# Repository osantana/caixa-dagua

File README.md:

# Caixa d'Água

Automação para controle de poço e caixa d'água da chácara

## Módulo central

* ESP32-WROOM rodando MicroPython
* Display TFT 2.4" 320x240 com Touch (ILI9341 + XPT2046)
* Módulo de Rádio HC-12
* RTC DS1307

### Instalação hidráulica

* Bóia automática na caixa d'água

## Módulo de controle

* Arduino Nano
* Módulo de Rádio HC-12
* Módulo de Relés 4 canais

### Instalação hidráulica

* Válvula eletrica 3 vias 220V
* Bomba hidráulica 220V

# Protocolo de comunicação

* SOURCE_ID: byte (0x00 = central)
* TARGET_ID: byte (0x00 = central)
* CHAIN_SIZE: byte
* CHAIN: list[byte] (devices que repassaram o pacote)
* COMMAND:
  * 0x00: RESET (reseta target)
  * 0x01: SET (seta parâmetro)
    * KEY: pascal-str
    * VALUE: pascal-str
  * 0x02: GET (recupera parâmetro)
    * KEY: pascal-str
    * VALUE: pascal-str
  * 0x03: RESPONSE (parâmetro recuperado)
    * KEY: pascal-str
    * VALUE: pascal-str
  * 0x04: NOTIFY (notificação)
    * PRIORITY: byte
    * NOTIFICATION: pascal-str

  * 0x11: READ
    * SENSOR_ID: byte (número do sensor para ler)
  * 0x12: INFO
    * SENSOR_ID: byte (número do sensor lido)
    * DATA: pascal-str

  * 0x20: START:
    * CHANNEL: byte (número do canal a ser parado)
    * TIMEOUT: uint (número de segundos de funcionamento deve ser diferente de 0)
  * 0x21: STOP (parada forçada. só deve ser usado em emergência)
    * CHANNEL: byte (número do canal a ser parado. 0xFF = todos)

* PARAMETERS: (dependente do comando)
* CHECKSUM: (a definir)

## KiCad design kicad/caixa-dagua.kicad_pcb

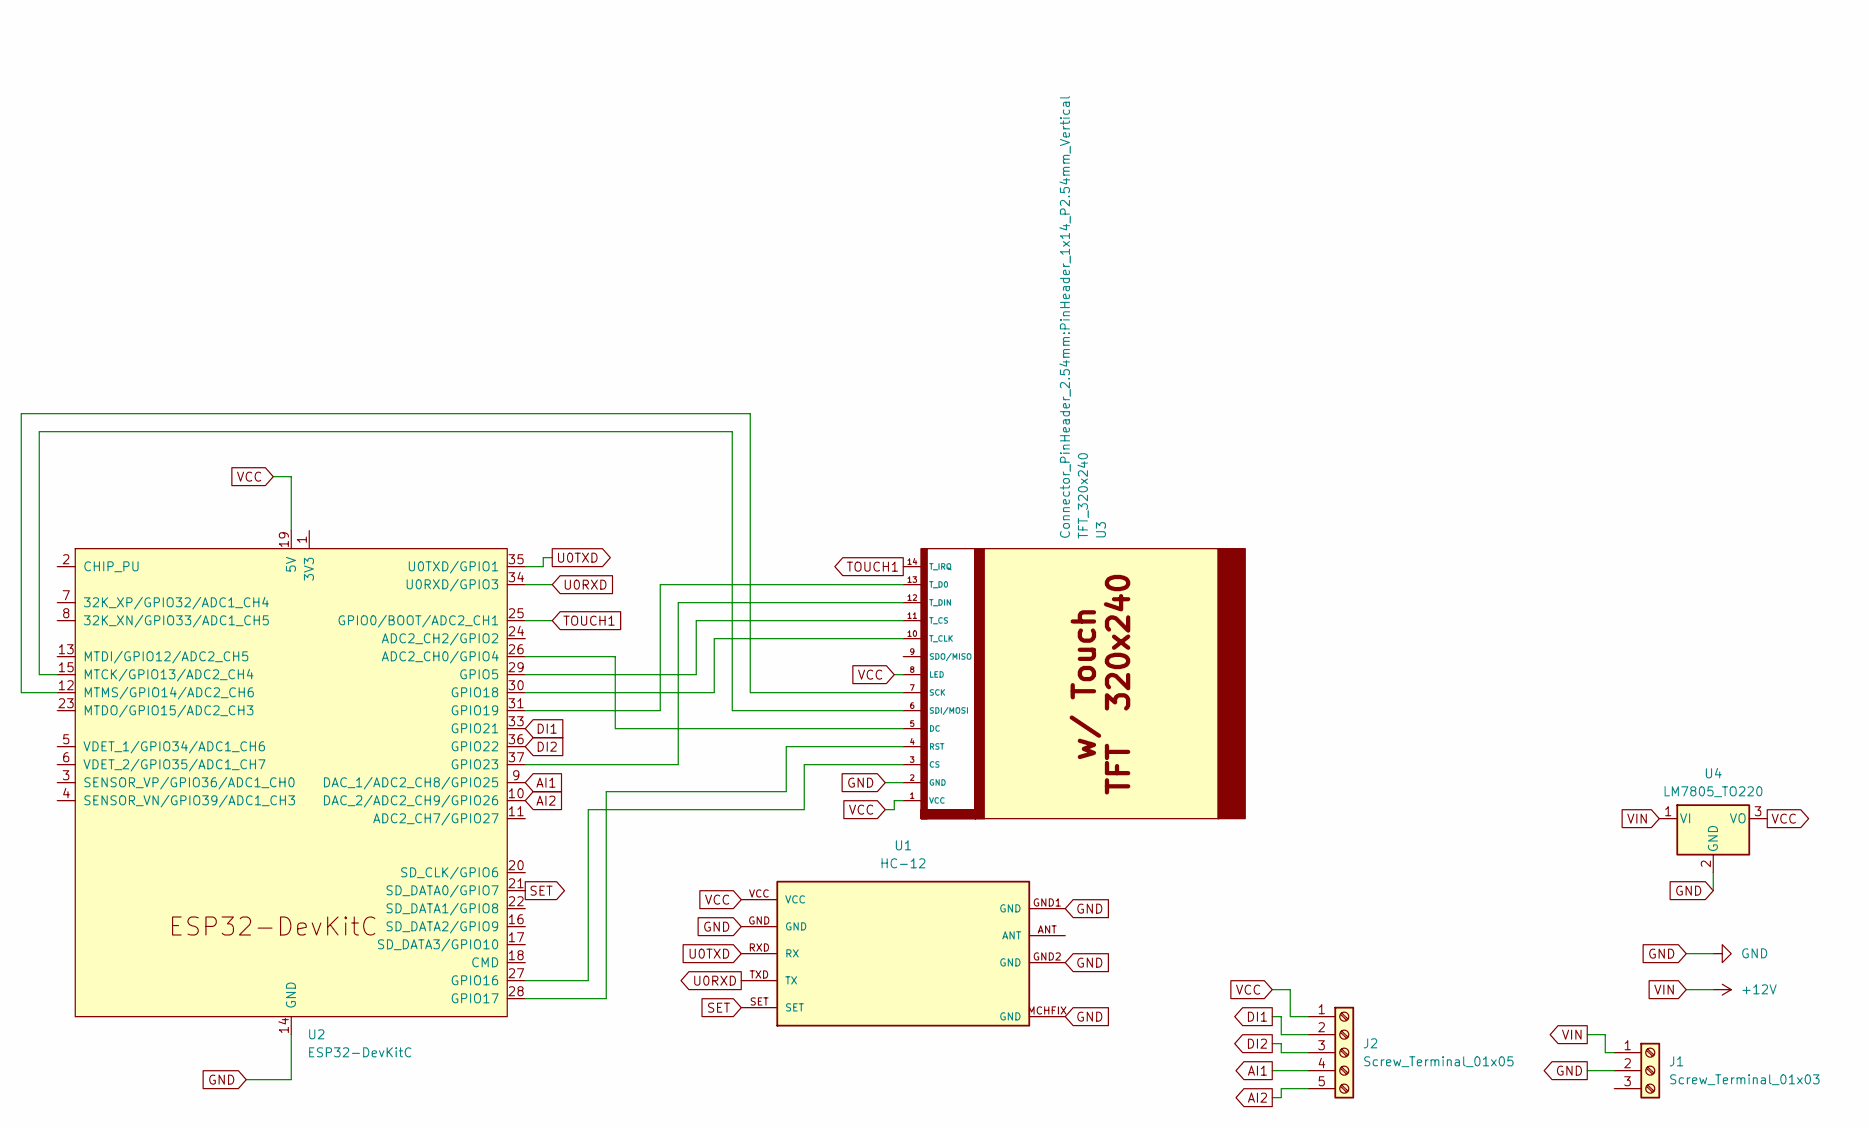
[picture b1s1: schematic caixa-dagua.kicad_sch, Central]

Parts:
J1: Screw_Terminal_01x03; TerminalBlock_bornier-3_P5.08mm
J2: Screw_Terminal_01x05; TerminalBlock_bornier-5_P5.08mm
U1: HC-12
U2: ESP32-DevKitC
U3: TFT_320x240; PinHeader_1x14_P2.54mm_Vertical
U4: LM7805_TO220; TO-220-3_Vertical

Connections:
AI1: J2.4, U2.9 (DAC_1/ADC2_CH8/GPIO25)
AI2: J2.5, U2.10 (DAC_2/ADC2_CH9/GPIO26)
DI1: J2.2, U2.33 (GPIO21)
DI2: J2.3, U2.36 (GPIO22)
GND: J1.2, U1.GND, U1.GND1 (GND), U1.GND2 (GND), U1.MCHFIX (GND), U2.14 (GND), U2.32 (GND), U2.38 (GND), U3.2 (GND), U4.2 (GND)
unnamed: U2.26 (ADC2_CH0/GPIO4), U3.5 (DC)
unnamed: U2.29 (GPIO5), U3.11 (T_CS)
unnamed: U2.27 (GPIO16), U3.3 (CS)
unnamed: U2.28 (GPIO17), U3.4 (RST)
unnamed: U2.30 (GPIO18), U3.10 (T_CLK)
unnamed: U2.31 (GPIO19), U3.13 (T_D0)
unnamed: U2.37 (GPIO23), U3.12 (T_DIN)
unnamed: U2.15 (MTCK/GPIO13/ADC2_CH4), U3.6 (SDI/MOSI)
unnamed: U2.12 (MTMS/GPIO14/ADC2_CH6), U3.7 (SCK)
SET: U1.SET, U2.21 (SD_DATA0/GPIO7)
TOUCH1: U2.25 (GPIO0/BOOT/ADC2_CH1), U3.14 (T_IRQ)
U0RXD: U1.TXD (TX), U2.34 (U0RXD/GPIO3)
U0TXD: U1.RXD (RX), U2.35 (U0TXD/GPIO1)
VCC: J2.1, U1.VCC, U2.19 (5V), U3.1 (VCC), U3.8 (LED), U4.3 (VO)
VIN: J1.1, U4.1 (VI)

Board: 2 copper layers, 6 parts (0 on the bottom side), 20 nets, no tracks yet.

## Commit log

2023-12-17 Add draft of the protocol
